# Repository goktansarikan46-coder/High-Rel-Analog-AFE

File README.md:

# High-Reliability Analog Front-End (AFE) Design

Bu proje, savunma sanayii standartları göz önünde bulundurularak, gürültülü (EMI) ortamlarda sensör verilerini güvenle işlemek için geliştirilmiş bir **Analog Ön-Uç (AFE)** devresidir. Yıldız Teknik Üniversitesi Biyomedikal Mühendisliği 2. sınıf öğrencisi olarak, teorik devre analizlerini profesyonel tasarım araçlarıyla pratiğe dökmeyi amaçladım.

## Proje Özellikleri
* **Giriş Koruma Katmanı:** +/- 15.7V clamping yapısı ile op-amp ve hassas bileşenler aşırı gerilime karşı korunmuştur.
* **Enstrümantasyon Amplifikatörü (InA):** 3-Op-Amp mimarisi ile yüksek CMRR (Ortak Mod Bastırma Oranı) sağlanmıştır.
* **Aktif Filtreleme:** 1 kHz kesim frekanslı 2. derece Sallen-Key Alçak Geçiren Filtre ile yüksek frekanslı parazitler süzülmüştür.
* **Üretim Analizi:** Monte Carlo analizi (100 run) ile komponent toleranslarının seri üretimdeki etkileri simüle edilmiştir.

## Kullanılan Teknolojiler
* **Simülasyon:** OrCAD PSpice Designer (Transient, AC Sweep, Noise, Monte Carlo)
* **PCB Tasarımı:** KiCad (2-Layer, Ground Plane, Decoupling Optimization)

## Klasör Yapısı
* `/Donanim`: KiCad şematik (.kicad_sch) ve PCB (.kicad_pcb) dosyaları.
* `/Simulasyon`: PSpice analiz çıktıları ve grafikler.
* `/Raporlar`: Detaylı proje raporu (PDF) ve 3D tasarım görselleri.

## Gelişim Notları
Bu proje benim için bir öğrenme sürecidir. Şu anki tasarımda genel amaçlı `uA741` op-amp kullanılmıştır. Projenin bir sonraki aşamasında, daha düşük gürültü (Low-noise) değerlerine sahip `OP07` veya `LT1028` gibi modellerle revize edilmesi planlanmaktadır.

---
**Hazırlayan:** Göktan Sarıkan (Yıldız Teknik Üniversitesi)

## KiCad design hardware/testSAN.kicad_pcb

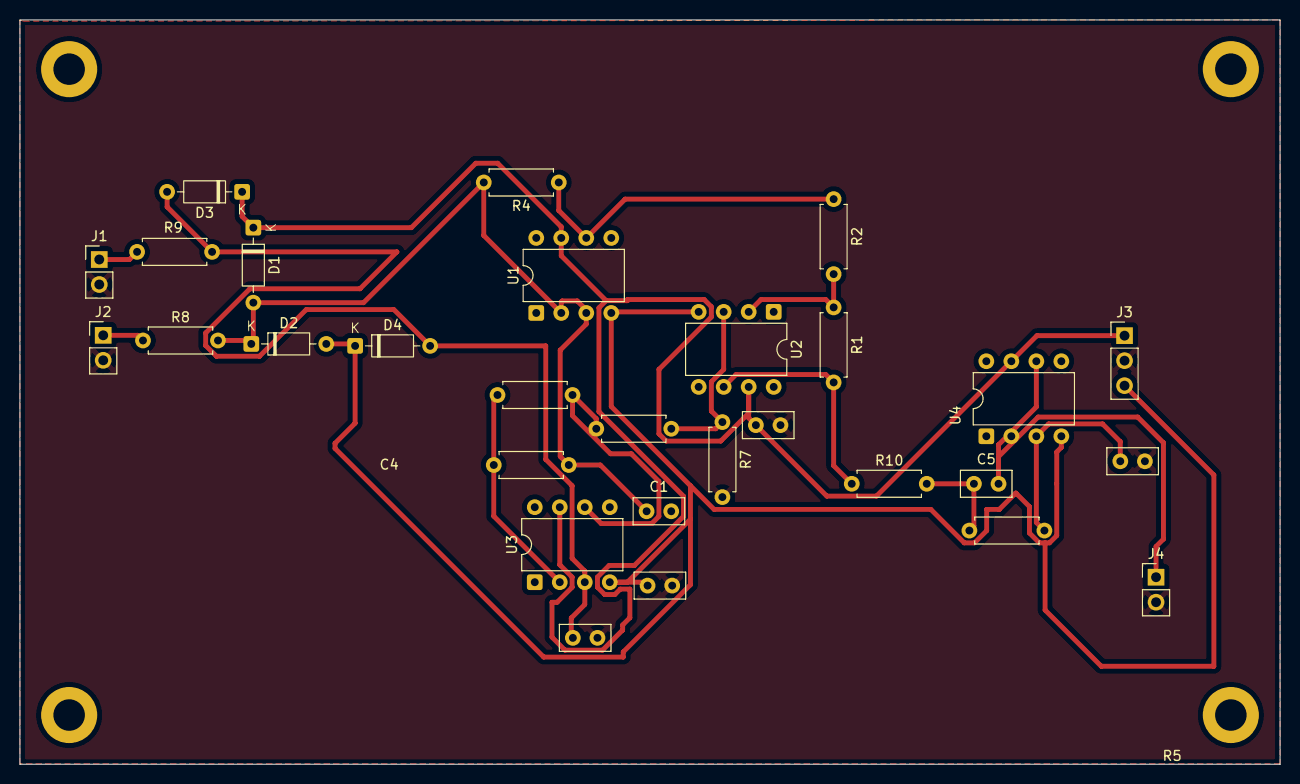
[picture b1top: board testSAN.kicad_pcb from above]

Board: 2 copper layers, 128.0 x 75.6 mm, 29 parts (0 on the bottom side), 16 nets.

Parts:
C1, C2, C3, C4: 100nF; C_Disc_D5.0mm_W2.5mm_P2.50mm
C5, C6: 10nF; C_Disc_D5.0mm_W2.5mm_P2.50mm
D1, D2, D3, D4: 1N4148; D_DO-35_SOD27_P7.62mm_Horizontal
J1, J2, J4: Conn_01x02_Socket; PinHeader_1x02_P2.54mm_Vertical
J3: Conn_01x03_Socket; PinHeader_1x03_P2.54mm_Vertical
R1, R2, R7: 10k; R_Axial_DIN0207_L6.3mm_D2.5mm_P7.62mm_Horizontal
R3: 10K; R_Axial_DIN0207_L6.3mm_D2.5mm_P7.62mm_Horizontal
R4, R6: 25k; R_Axial_DIN0207_L6.3mm_D2.5mm_P7.62mm_Horizontal
R5: 5.5k; R_Axial_DIN0207_L6.3mm_D2.5mm_P7.62mm_Horizontal
R8, R9: 1k; R_Axial_DIN0207_L6.3mm_D2.5mm_P7.62mm_Horizontal
R10, R11: 16k; R_Axial_DIN0207_L6.3mm_D2.5mm_P7.62mm_Horizontal
U1, U2, U3, U4: LM741; DIP-8_W7.62mm

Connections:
+15V: C3.1, D1.1 (K), D3.1 (K), J3.1, U1.7 (V+), U2.7 (V+), U3.7 (V+), U4.7 (V+)
-15V: C4.1, D2.2 (A), D4.1 (K), J3.3, U1.4 (V-), U2.4 (V-), U3.4 (V-), U4.4 (V-)
GND: C1.2, C2.2, C3.2, C4.2, C6.2, J1.2, J2.2, J3.2, J4.2, R7.2
unnamed: C5.1, R10.2, R11.1
unnamed: C1.1, D1.2 (A), D2.1 (K), R4.2, R5.1, R8.2, U1.2 (-), U1.3 (+)
unnamed: C2.1, D3.2 (A), D4.2 (A), R9.2, U3.3 (+)
unnamed: J1.1, R9.1
unnamed: J2.1, R8.1
unnamed: C5.2, J4.1, U4.2 (-), U4.6
unnamed: R1.2, R10.1, U2.6
unnamed: R2.1, R4.1, U1.6
unnamed: R3.1, R6.2, U3.6
unnamed: R3.2, R7.1, U2.3 (+)
unnamed: R1.1, R2.2, U2.2 (-)
unnamed: R5.2, R6.1, U3.2 (-)
unnamed: C6.1, R11.2, U4.3 (+)

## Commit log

2025-12-28 Revise README with project details and features
    Updated project description and added features, technologies, and folder structure sections.
2025-12-28 Update README.md for project features and technologies
